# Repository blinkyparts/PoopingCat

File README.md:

# Pooping Cat

What are you staring at? This pooping cat will stare back! The eyes are glowing in all colours of the rainbow due to RGB-LEDs on the back. The soldering kit is very simple and easy to assamble.

The RGB-Effect looks like this, but much better in real :)

- Status: **Complete**
- Difficulty: **2/5**

### Parts List

| Description                   | Quantity |
|-------------------------------|----------|
| RGB LEDs 5mm                  |     2    |
| Button (SMD)                  |     1    |
| CR2032 Battery Holder (SMD)   |     1    |
| CR2032 Battery (not included) |     1    |

### Manual
You can find the manual and pictures of every step here: https://github.com/Binary-Kitchen/SolderingTutorial

### Copyright and Authorship

- Board: [CC-BY-NC-SA 4.0](https://creativecommons.org/licenses/by-nc-sa/4.0/deed) - blinkyparts GmbH
- Cat SVG [CC-BY-SA](https://creativecommons.org/licenses/by-sa/4.0/) - [Pooping Cat by Denis Sazhin from the Noun Project](https://thenounproject.com/icon/pooping-cat-601648/) (We've bought a licence, you should honor the artist work too!)

### Buy Soldering Kits
If you want to buy the parts and PCB for a soldering kit you can find everything here: [shop.blinkyparts.com](https://shop.blinkyparts.com/de/Katze-in-der-Box-Wunderbar-einfacher-Bausatz-zum-loeten-und-lieben/blink236842)

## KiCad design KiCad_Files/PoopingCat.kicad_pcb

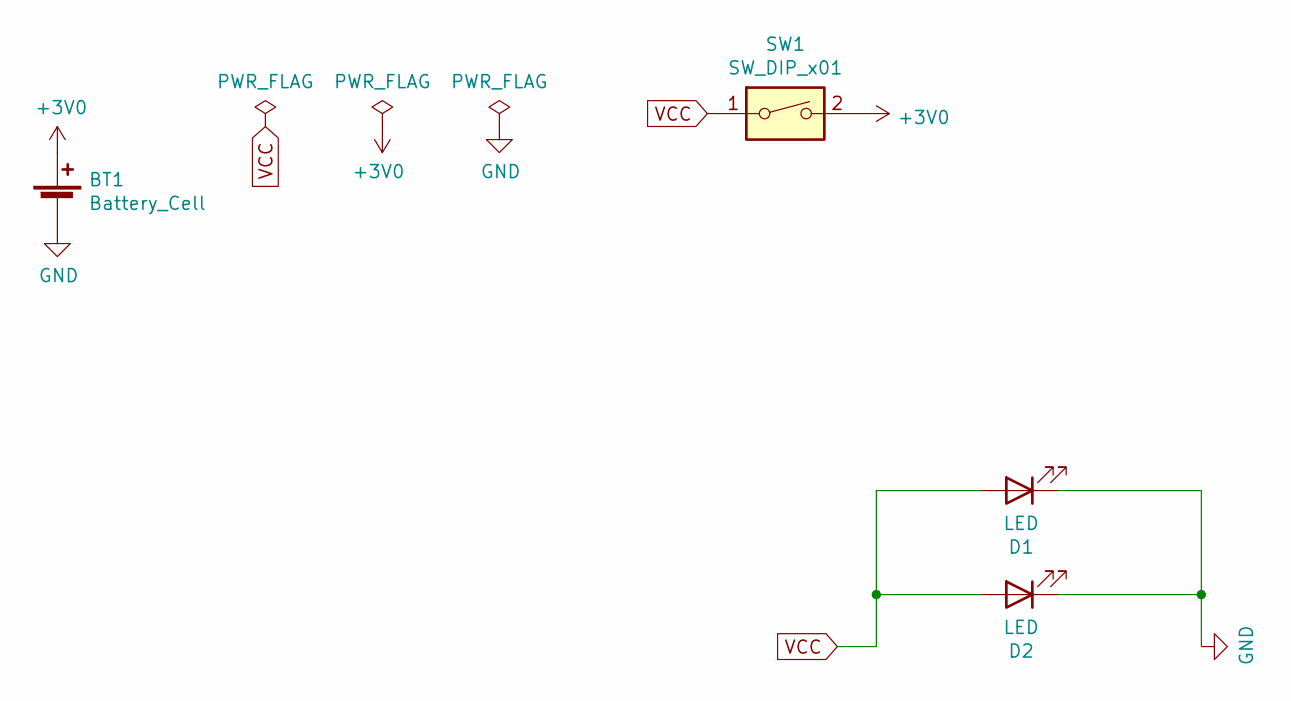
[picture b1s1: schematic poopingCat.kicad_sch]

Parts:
BT1: Battery_Cell; BatteryHolder_Keystone_1060_1x2032_HandSoldering
D1, D2: LED; 5mm_SMD-Pad
SW1: SW_DIP_x01; Push_Button

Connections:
+3V0: BT1.1 (+), SW1.2
GND: BT1.2 (-), D1.1 (K), D2.1 (K)
VCC: D1.2 (A), D2.2 (A), SW1.1

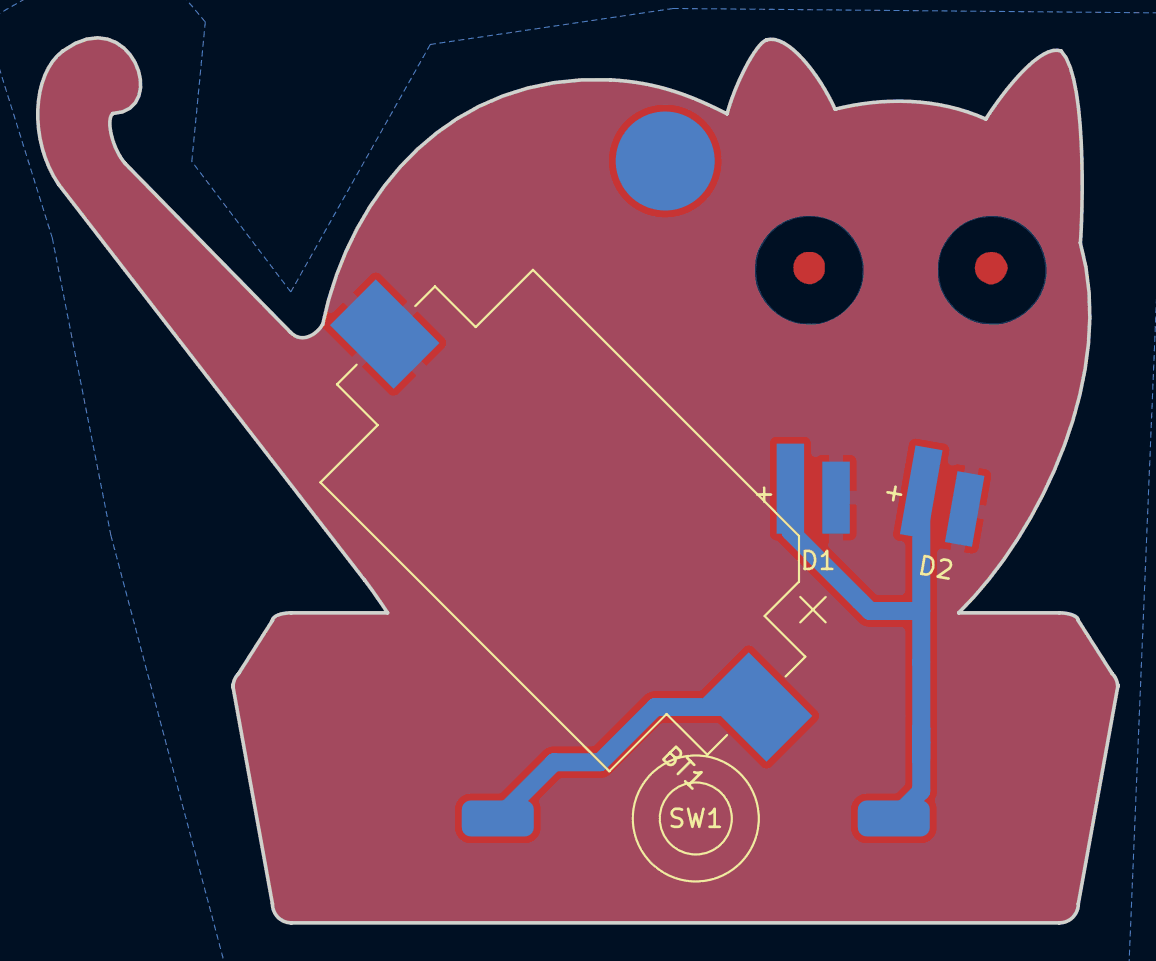
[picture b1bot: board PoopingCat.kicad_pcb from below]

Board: 2 copper layers, 60.0 x 49.2 mm, 9 parts (8 on the bottom side), 3 nets.

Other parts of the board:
BP1: MountingHole_2.2mm_M2
Ref**: Val**; catbox02
blinkyparts_logo_10mm: G***; logo_10mm
ce-symbol_mask_3mm: G***; ce-icon_3mm
weee-symbol_mask_3mm: G***; weee-icon_3mm

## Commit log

2026-01-16 inital commit for version 1.0
2026-01-16 further improvements for blinkyparts. and updated readme
2026-01-18 added github specific readme and updated readme.md
2026-01-18 updated licence file
2026-06-07 fixed error in readme
2026-06-07 minor changes
